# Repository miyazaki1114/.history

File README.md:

# 冗長電源基板（radundant_circuit V1.0）

2本のバッテリーから電源を取り込み、片方を外しても、残ったバッテリーから給電を続けるための基板です。ロボット搭載PCへの給電を想定しています。

本書は、リポジトリ内の回路図・PCBデータと設計メモをもとにしています。回路の接続は確認済みですが、実装状態・連続許容電流・PCの無停電動作は実機での確認が必要です。

## 接続構成

```text
バッテリー1 ＋ → J1(IN1) → F1 → D1の素子1 ─┐
                                             ├→ J3(OUT) → 外付けDC/DC → PC
バッテリー2 ＋ → J2(IN2) → F2 → D1の素子2 ─┘
バッテリー1・2の－、J3の－は共通GND
```

- 設計上の想定電池は **6S LiPo × 2本**（1本あたり公称22.2 V、満充電25.2 V）です。これは基板の動作保証範囲を示すものではありません。
- D1（RBQ30NS65ATL）の2つのダイオードで電源を合流します。基本的に電圧の高い側から給電され、電圧が近い場合は両方から流れることがあります。IN1を優先する制御はありません。
- OUTの電圧は、給電中の入力電圧からダイオードの電圧降下を引いた値になります。**この基板だけでは19 Vに変換・安定化しません。** PCには適切な外付けDC/DCを介して接続してください。
- バッテリー充電回路や、低電圧時に自動遮断する回路はありません。

## 端子と極性

PCB上のコネクタは、いずれも `AMASS_XT60-F_1x02_P7.20mm_Vertical` のフットプリントです。

| 端子 | 基板表示 | 用途 | 1番ピン | 2番ピン |
| --- | --- | --- | --- | --- |
| J1 | IN1 | バッテリー1入力 | GND（－） | バッテリー1の＋（F1の手前） |
| J2 | IN2 | バッテリー2入力 | GND（－） | バッテリー2の＋（F2の手前） |
| J3 | OUT | 外付けDC/DCの入力へ | GND（－） | 合流後の出力＋ |

ピン番号は回路図・PCBのパッド番号です。見る面によって左右が反転するため、コネクタの左右だけで極性を判断せず、PCBデータと実物の導通を確認してください。OUTへバッテリーを接続しないでください。

## LEDの見方

| LED | 対応抵抗 | 表示する電圧 |
| --- | --- | --- |
| D2 | R1 | IN1側のヒューズF1通過後の電圧 |
| D3 | R2 | IN2側のヒューズF2通過後の電圧 |
| D5 | R3 | OUTの電圧 |

LEDは電圧の有無の目安です。点灯だけでは、電池残量や、その入力から実際に負荷へ電流が流れているかは判断できません。R1～R3の値は図面では `R` のままなので、使用するLEDと最大電圧に合わせて抵抗値・許容損失を決めて実装してください。

## 初回使用前の確認

1. F1・F2に適切なヒューズを取り付けます。図面では容量未指定です。負荷電流、突入電流、配線・コネクタ・基板の許容電流に合わせて選定してください。
2. D1、TVSのD4、LED、電解コンデンサC1の向きと、はんだ付けを確認します。C1の1番ピンが＋、2番ピンがGNDです。
3. 電源を外した状態で各コネクタの極性と配線を確認し、はんだブリッジなどによる＋とGNDの短絡がないことを確認します。コンデンサ充電による一時的な導通表示と短絡を区別してください。
4. まず電流制限付き電源と小さな試験負荷で、IN1だけ・IN2だけの各条件でOUTに給電されることを確認します。
5. 外付けDC/DCの入力許容範囲と、PCに必要な出力電圧・極性・容量を確認します。設計メモには19 V出力を想定していますが、実際のPCの仕様を優先してください。
6. 想定負荷でダイオード・ヒューズ・コネクタ・配線の温度とOUT電圧を確認します。部品単体の電流定格を基板全体の連続許容電流として扱わないでください。

## 通常の使い方

1. 負荷の電源を切り、J3（OUT）を外付けDC/DCの入力へ接続します。
2. バッテリー1をJ1（IN1）へ、バッテリー2をJ2（IN2）へ接続します。
3. IN1・IN2・OUTの電圧を確認します。LEDを実装している場合は、D2・D3・D5の点灯も確認します。
4. DC/DCの出力がPCの指定電圧・極性になっていることを確認して、PCへの給電を開始します。
5. 使用中は両方の電池残量を別途監視します。本基板には過放電を防止する自動遮断機能はありません。

## 給電を続けながら電池を交換する

1. 残す側の電池が接続され、ヒューズが正常で、**その1本だけで負荷全体を動かせること**を確認します。
2. 交換する側の電池だけを外します。両方を同時に外さないでください。
3. 極性を確認した交換用電池を、空いた入力へ接続します。
4. 入力・出力電圧と、負荷が正常動作していることを確認します。

電池交換時の無停電動作は、残る電池の電圧・内部抵抗、負荷、DC/DCの特性に依存します。事前に試験負荷で切替時のOUT電圧低下とDC/DCの出力を確認し、その後PCで停止・再起動しないことを確認してください。C1があることだけで無停電を保証するものではありません。

## 実装部品と未確定事項

| 部品 | 現在の図面上の値・用途 | 使用前に確認すること |
| --- | --- | --- |
| D1 | RBQ30NS65ATL／2入力のダイオードOR | 放熱、実負荷での電圧降下・温度 |
| F1・F2 | 各入力のヒューズ | 定格電流・定格電圧・遮断容量・突入への適合 |
| C1 | 4700 µF／出力平滑 | 耐圧・極性・リプル電流、接続時の突入電流 |
| C2 | 1 µF／出力デカップリング | 耐圧、実使用電圧での容量 |
| C3 | 0.1 µF／出力デカップリング | 耐圧 |
| D4 | SMBJ26A／OUT–GND間のTVS | サージ時のクランプ電圧と後段機器の許容電圧の整合 |
| D2・D3・D5 | 入力・出力表示用LED | LEDの型番・極性 |
| R1～R3 | LEDの直列抵抗（値未指定） | 抵抗値・許容損失 |

D4はサージ抑制用です。OUTを常に26 V以下に保つ回路や、過電圧で給電を切断する回路ではありません。設計メモにある「DC/DC入力上限30 V」は未確認情報のため、使用するDC/DCの資料で確認してください。

D1は出力から入力側への逆流を抑える構成ですが、入力の逆接続保護を保証するものではありません。バッテリーは必ず極性を確認して接続してください。

## 困ったとき

| 症状 | 確認する箇所 |
| --- | --- |
| 片側の入力LEDが消えている | 対応する電池・配線・F1/F2・LEDと抵抗の実装 |
| 入力LEDは点くがOUTが出ない | D1の向き・はんだ付け・OUT配線・負荷の短絡 |
| OUTは出るがPCが動かない | DC/DCの入力範囲、出力電圧・極性・容量、PC側の電源仕様 |
| 電池を外すとPCが落ちる | 残る電池の電圧・供給能力、ヒューズ、接点、切替時の電圧低下 |
| 部品や配線が過熱する | 使用を止め、負荷電流・接触不良・放熱・短絡を確認 |

## 設計ファイル

- [KiCadプロジェクト](radundant_circuit.kicad_pro)
- [回路図](radundant_circuit.kicad_sch)
- [PCB](radundant_circuit.kicad_pcb)
- [設計検討メモ](memo/冗長回路_メモ.md)（初期案を含むため、現行の部品値は回路図を確認）

図面はKiCad 10.0で保存されています。F1/F2にはカスタムフットプリント `IMRC_footprint:FUSE_SOCKET` を使っています。PCBには形状が保存されていますが、ライブラリから更新する際は対応するライブラリが必要です。

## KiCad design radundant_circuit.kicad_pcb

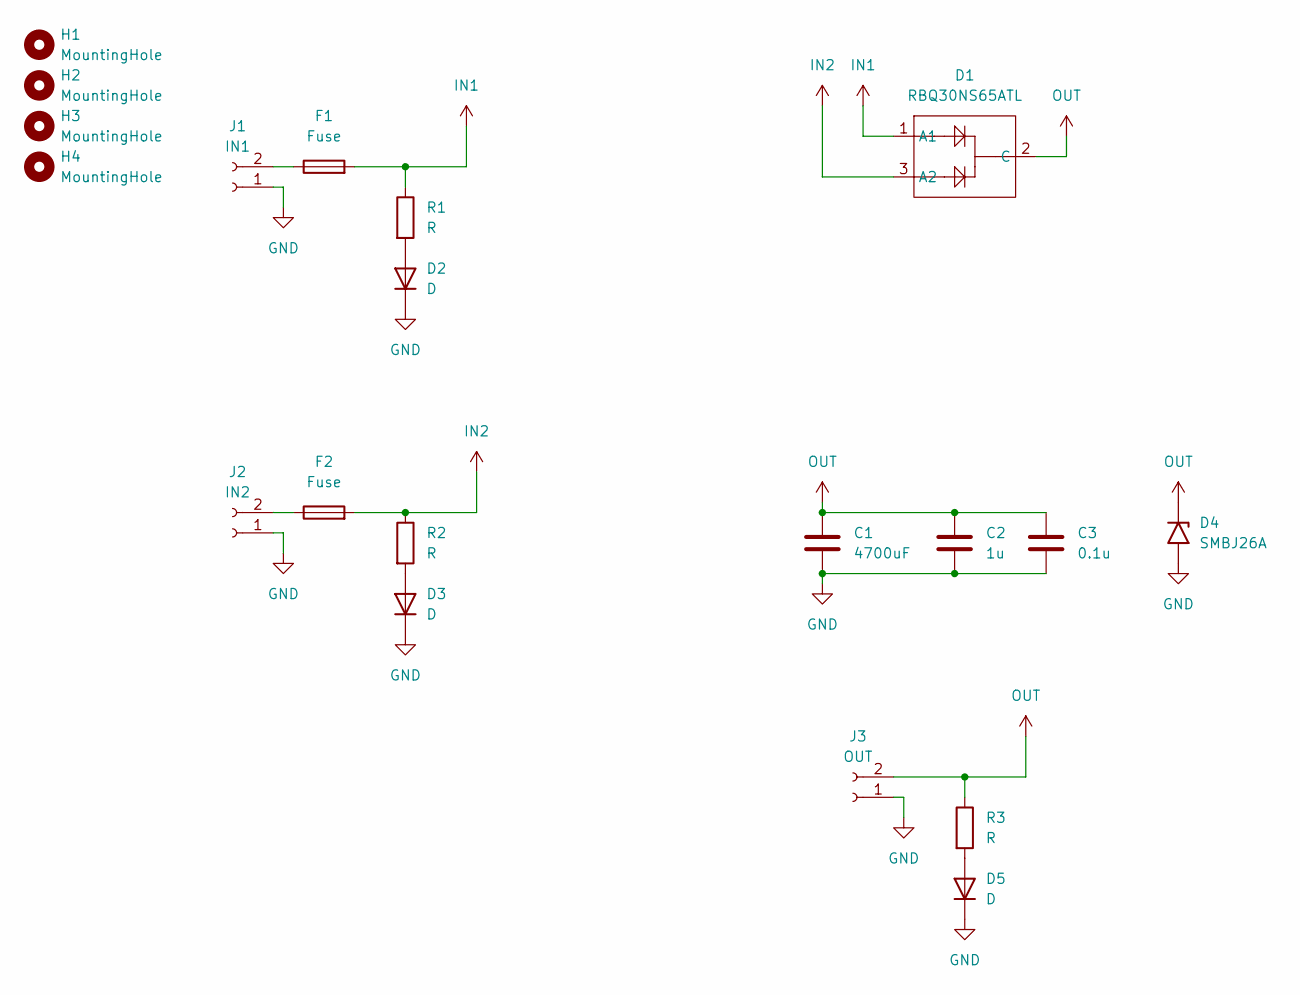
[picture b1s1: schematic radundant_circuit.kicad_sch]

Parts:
C1: 4700uF; CP_Radial_D18.0mm_P7.50mm
C2: 1u; C_0603_1608Metric_Pad1.08x0.95mm_HandSolder
C3: 0.1u; C_0603_1608Metric_Pad1.08x0.95mm_HandSolder
D1: RBQ30NS65ATL; TO-263-2
D2, D3, D5: D; LED_0603_1608Metric_Pad1.05x0.95mm_HandSolder
D4: SMBJ26A; D_SMB
F1, F2: Fuse; FUSE_SOCKET
H1, H2, H3, H4: MountingHole; MountingHole_3.2mm_M3
J1: IN1; AMASS_XT60-F_1x02_P7.20mm_Vertical
J2: IN2; AMASS_XT60-F_1x02_P7.20mm_Vertical
J3: OUT; AMASS_XT60-F_1x02_P7.20mm_Vertical
R1, R2, R3: R; R_0603_1608Metric_Pad0.98x0.95mm_HandSolder

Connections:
GND: C1.2, C2.2, C3.2, D2.1 (K), D3.1 (K), D4.2 (A2), D5.1 (K), J1.1, J2.1, J3.1
IN1: D1.1 (A1), F1.2, R1.1
IN2: D1.3 (A2), F2.2, R2.1
unnamed: D2.2 (A), R1.2
unnamed: D3.2 (A), R2.2
unnamed: D5.2 (A), R3.2
unnamed: F1.1, J1.2
unnamed: F2.1, J2.2
OUT: C1.1, C2.1, C3.1, D1.2 (C), D4.1 (A1), J3.2, R3.1

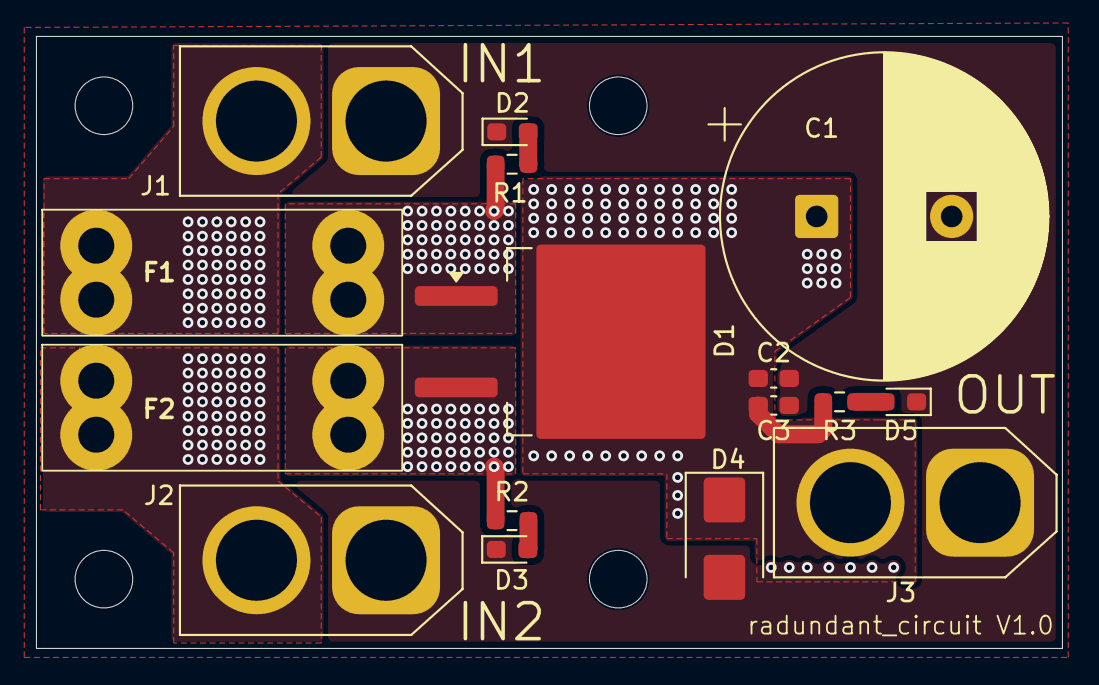
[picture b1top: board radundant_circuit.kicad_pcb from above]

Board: 2 copper layers, 57.0 x 34.0 mm, 20 parts (0 on the bottom side), 9 nets.
